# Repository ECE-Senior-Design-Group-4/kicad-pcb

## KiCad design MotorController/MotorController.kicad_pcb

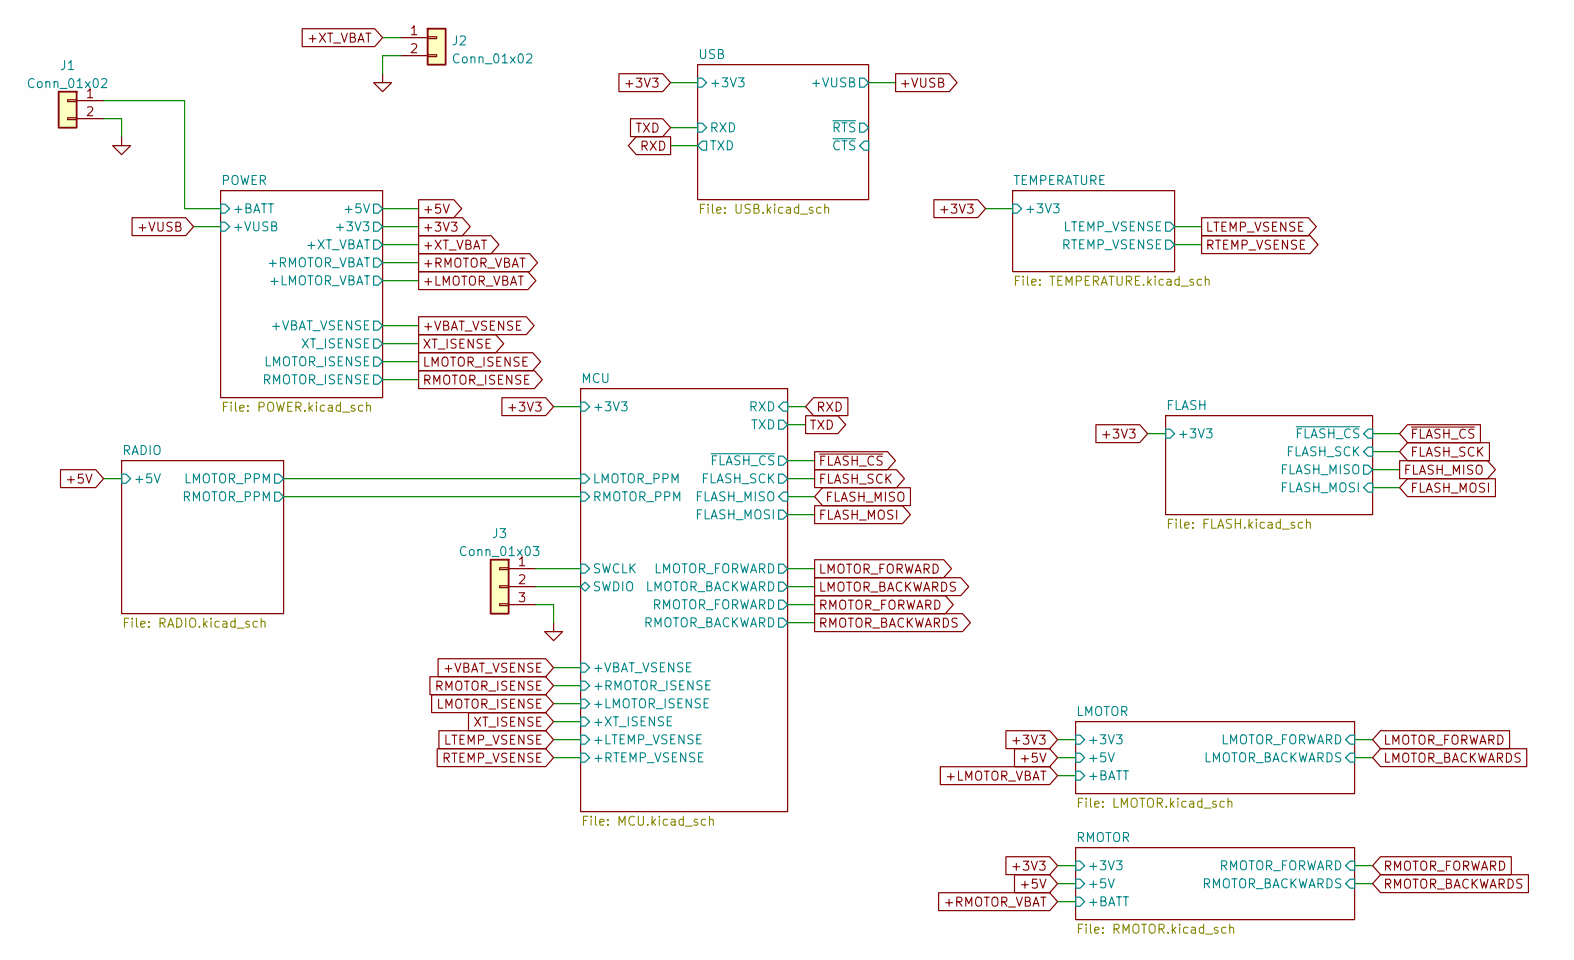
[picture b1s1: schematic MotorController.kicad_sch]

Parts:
J1, J2: Conn_01x02; PinHeader_1x02_P2.54mm_Vertical
J3: Conn_01x03; PinHeader_1x03_P2.54mm_Vertical

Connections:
+XT_VBAT: J2.1; also elsewhere on the board
/MCU/SWCLK: J3.1; also elsewhere on the board
/MCU/SWDIO: J3.2; also elsewhere on the board
GND: J1.2, J2.2, J3.3; also elsewhere on the board

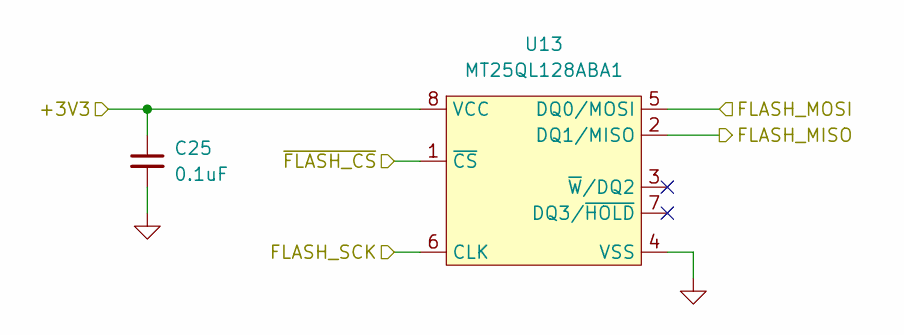
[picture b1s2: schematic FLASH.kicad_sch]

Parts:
C25: 0.1uF; C_0402_1005Metric; MPN CC0402KPX7R8BB104
U13: MT25QL128ABA1; SOIC127P780X200-8N; MPN MT25QL128ABA1

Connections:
+3V3: C25.1, U13.8 (VCC); also elsewhere on the board
FLASH_MISO: U13.2 (DQ1/MISO); also elsewhere on the board
FLASH_MOSI: U13.5 (DQ0/MOSI); also elsewhere on the board
FLASH_SCK: U13.6 (CLK); also elsewhere on the board
GND: C25.2, U13.4 (VSS); also elsewhere on the board
~FLASH_CS: U13.1 (~CS); also elsewhere on the board

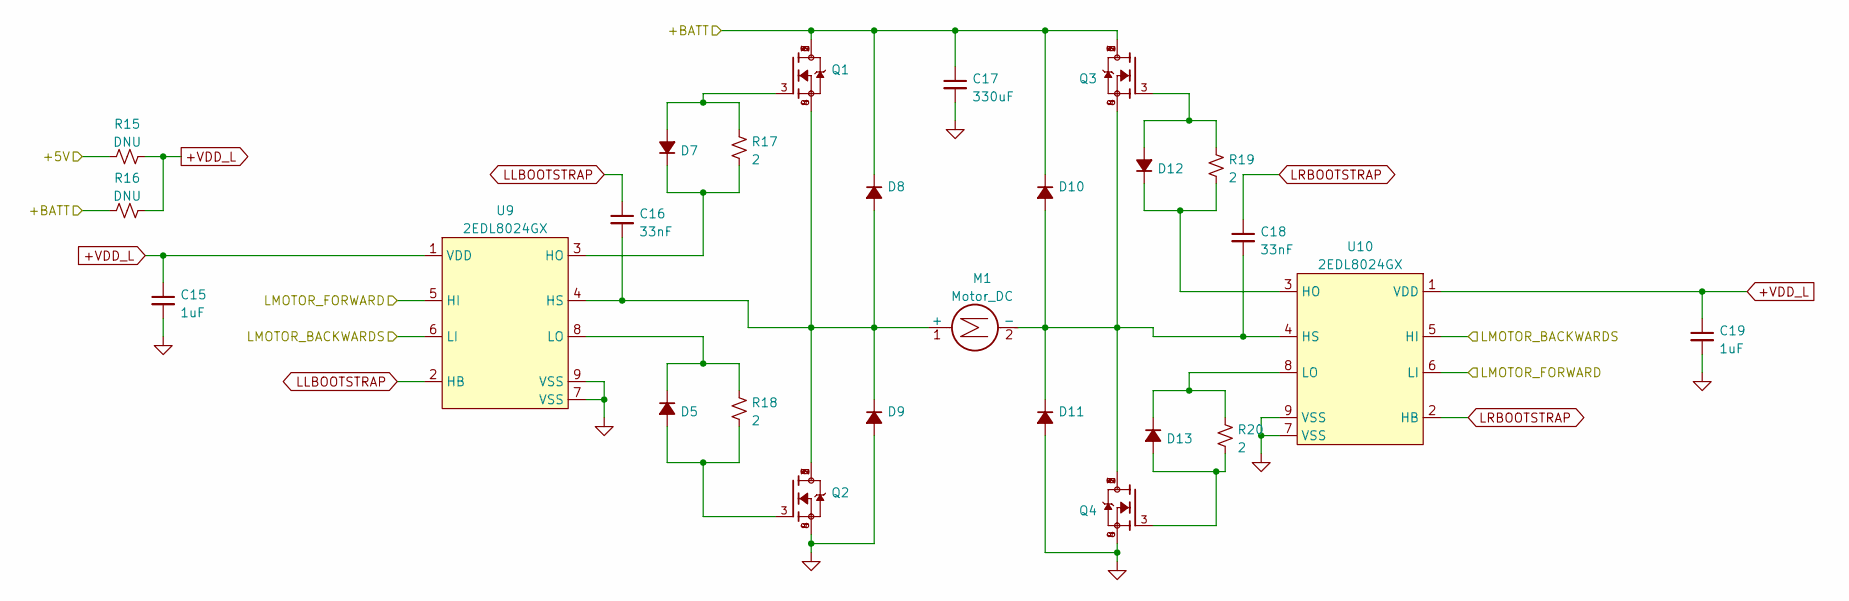
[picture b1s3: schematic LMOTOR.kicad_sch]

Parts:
C15, C19: 1uF; C_0402_1005Metric; MPN CC0402KRX5R8BB105
C16, C18: 33nF; C_0402_1005Metric; MPN CC0402KRX7R9BB333
C17: 330uF; PinHeader_1x02_P2.54mm_Vertical
D5, D7, D12, D13: D_Small_Filled; D_SOD-323; MPN NSR0530HT1G
D8, D9, D10, D11: D_Small_Filled; TO-277B; MPN MBR1560S
M1: Motor_DC; PinHeader_1x02_P2.54mm_Vertical
Q1, Q2, Q3, Q4: SSM6K513NU-LF; TRANS_SSM6K513NU-LF
R15, R16: DNU; R_0402_1005Metric; MPN RC0402JR-0710KL
R17, R18, R19, R20: 2; R_0402_1005Metric; MPN RC0402FR-072RL
U9, U10: 2EDL8024GX; DFN-8-1EP_4x4mm_P0.8mm_EP2.3x3.24mm; MPN 2EDL8024GX

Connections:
+5V: R15.1; also elsewhere on the board
+LMOTOR_VBAT: C17.1, D8.1 (K), D10.1 (K), Q1.1, Q1.2, Q1.5, Q1.6, Q1.7, Q3.1, Q3.2, Q3.5, Q3.6, Q3.7, R16.1; also elsewhere on the board
+VDD_L: C15.1, C19.1, R15.2, R16.2, U9.1 (VDD), U10.1 (VDD)
GND: C15.2, C17.2, C19.2, D9.2 (A), D11.2 (A), Q2.4, Q2.8, Q4.4, Q4.8, U9.7 (VSS), U9.9 (VSS), U10.7 (VSS), U10.9 (VSS); also elsewhere on the board
LLBOOTSTRAP: C16.1, U9.2 (HB)
LMOTOR_BACKWARDS: U9.6 (LI), U10.5 (HI); also elsewhere on the board
LMOTOR_FORWARD: U9.5 (HI), U10.6 (LI); also elsewhere on the board
LRBOOTSTRAP: C18.1, U10.2 (HB)
unnamed: C16.2, D8.2 (A), D9.1 (K), M1.1 (+), Q1.4, Q1.8, Q2.1, Q2.2, Q2.5, Q2.6, Q2.7, U9.4 (HS)
unnamed: C18.2, D10.2 (A), D11.1 (K), M1.2 (-), Q3.4, Q3.8, Q4.1, Q4.2, Q4.5, Q4.6, Q4.7, U10.4 (HS)
unnamed: D5.1 (K), R18.1, U9.8 (LO)
unnamed: D5.2 (A), Q2.3, R18.2
unnamed: D7.1 (K), R17.2, U9.3 (HO)
unnamed: D7.2 (A), Q1.3, R17.1
unnamed: D12.1 (K), R19.2, U10.3 (HO)
unnamed: D12.2 (A), Q3.3, R19.1
unnamed: D13.1 (K), R20.1, U10.8 (LO)
unnamed: D13.2 (A), Q4.3, R20.2

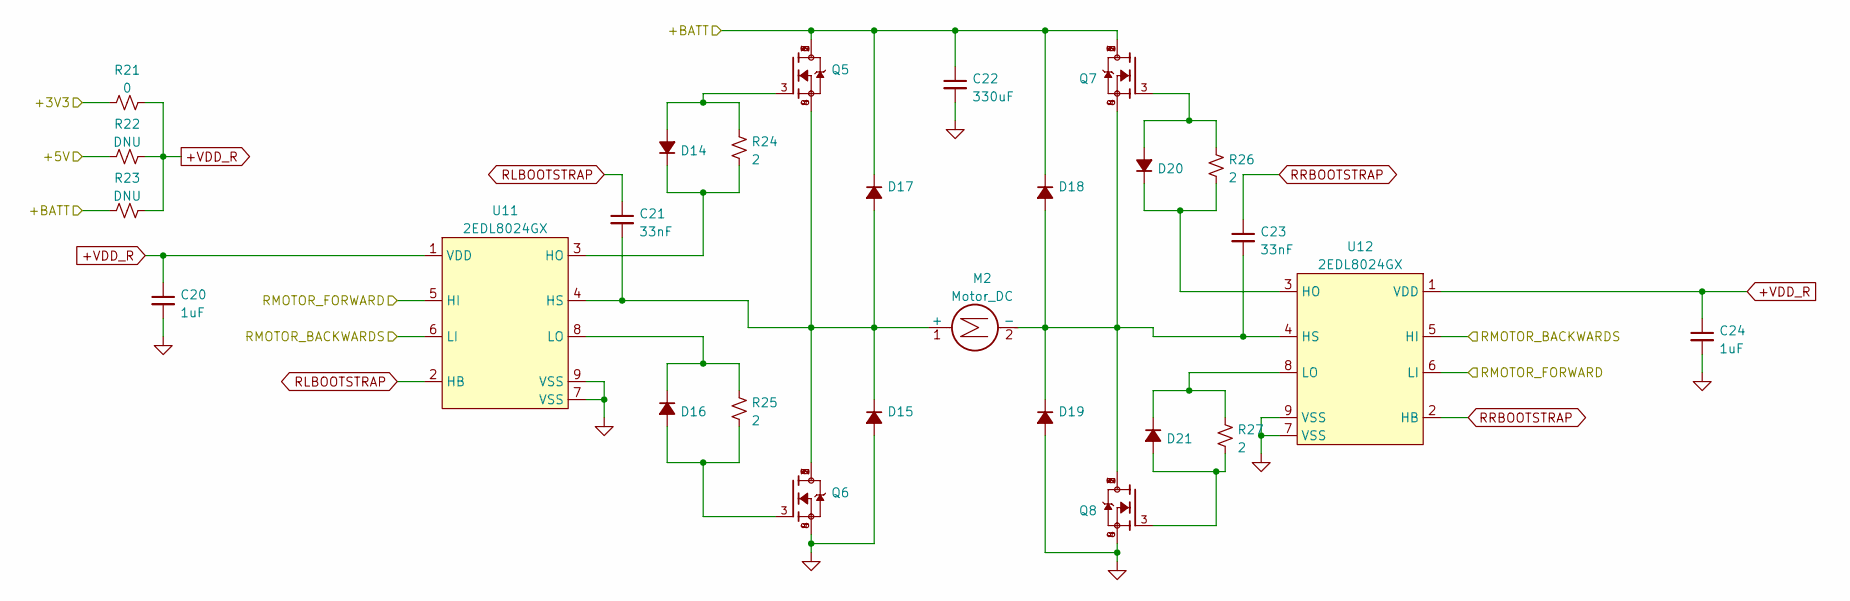
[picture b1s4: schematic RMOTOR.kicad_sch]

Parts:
C20, C24: 1uF; C_0402_1005Metric; MPN CC0402KRX5R8BB105
C21, C23: 33nF; C_0402_1005Metric; MPN CC0402KRX7R9BB333
C22: 330uF; PinHeader_1x02_P2.54mm_Vertical
D14, D16, D20, D21: D_Small_Filled; D_SOD-323; MPN NSR0530HT1G
D15, D17, D18, D19: D_Small_Filled; TO-277B; MPN MBR1560S
M2: Motor_DC; PinHeader_1x02_P2.54mm_Vertical
Q5, Q6, Q7, Q8: SSM6K513NU-LF; TRANS_SSM6K513NU-LF
R21: 0; R_0402_1005Metric; MPN RC0402JR-070RL
R22, R23: DNU; R_0402_1005Metric; MPN RC0402JR-0710KL
R24, R25, R26, R27: 2; R_0402_1005Metric; MPN RC0402FR-072RL
U11, U12: 2EDL8024GX; DFN-8-1EP_4x4mm_P0.8mm_EP2.3x3.24mm; MPN 2EDL8024GX

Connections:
+5V: R22.1; also elsewhere on the board
+VDD_R: C20.1, C24.1, R21.2, R22.2, R23.2, U11.1 (VDD), U12.1 (VDD)
GND: C20.2, C22.2, C24.2, D15.2 (A), D19.2 (A), Q6.4, Q6.8, Q8.4, Q8.8, U11.7 (VSS), U11.9 (VSS), U12.7 (VSS), U12.9 (VSS); also elsewhere on the board
unnamed: C21.2, D15.1 (K), D17.2 (A), M2.1 (+), Q5.4, Q5.8, Q6.1, Q6.2, Q6.5, Q6.6, Q6.7, U11.4 (HS)
unnamed: C23.2, D18.2 (A), D19.1 (K), M2.2 (-), Q7.4, Q7.8, Q8.1, Q8.2, Q8.5, Q8.6, Q8.7, U12.4 (HS)
unnamed: D14.1 (K), R24.2, U11.3 (HO)
unnamed: D14.2 (A), Q5.3, R24.1
unnamed: D16.1 (K), R25.1, U11.8 (LO)
unnamed: D16.2 (A), Q6.3, R25.2
unnamed: D20.1 (K), R26.2, U12.3 (HO)
unnamed: D20.2 (A), Q7.3, R26.1
unnamed: D21.1 (K), R27.1, U12.8 (LO)
unnamed: D21.2 (A), Q8.3, R27.2
RLBOOTSTRAP: C21.1, U11.2 (HB)
RMOTOR_BACKWARDS: U11.6 (LI), U12.5 (HI); also elsewhere on the board
RMOTOR_FORWARD: U11.5 (HI), U12.6 (LI); also elsewhere on the board
RRBOOTSTRAP: C23.1, U12.2 (HB)

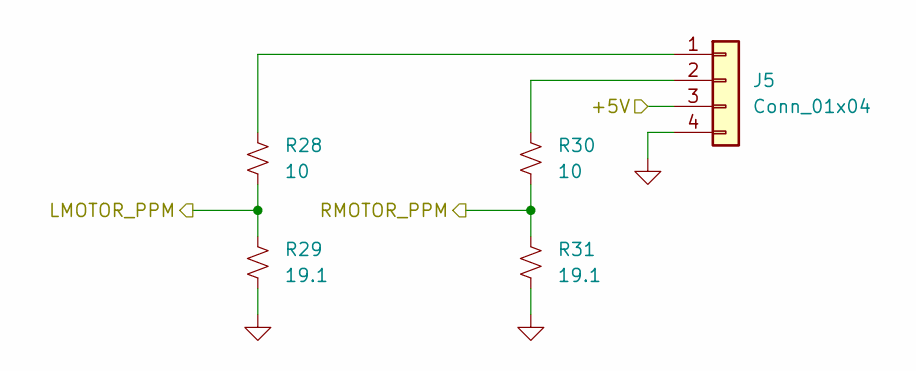
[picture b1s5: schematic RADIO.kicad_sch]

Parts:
J5: Conn_01x04; PinHeader_1x04_P2.54mm_Vertical
R28, R30: 10; R_0402_1005Metric; MPN RC0402JR-0710RL
R29, R31: 19.1; R_0402_1005Metric; MPN RC0402FR-0719R1L

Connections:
+5V: J5.3; also elsewhere on the board
/MCU/LMOTOR_PPM: R28.2, R29.1; also elsewhere on the board
/MCU/RMOTOR_PPM: R30.2, R31.1; also elsewhere on the board
GND: J5.4, R29.2, R31.2; also elsewhere on the board
unnamed: J5.1, R28.1
unnamed: J5.2, R30.1

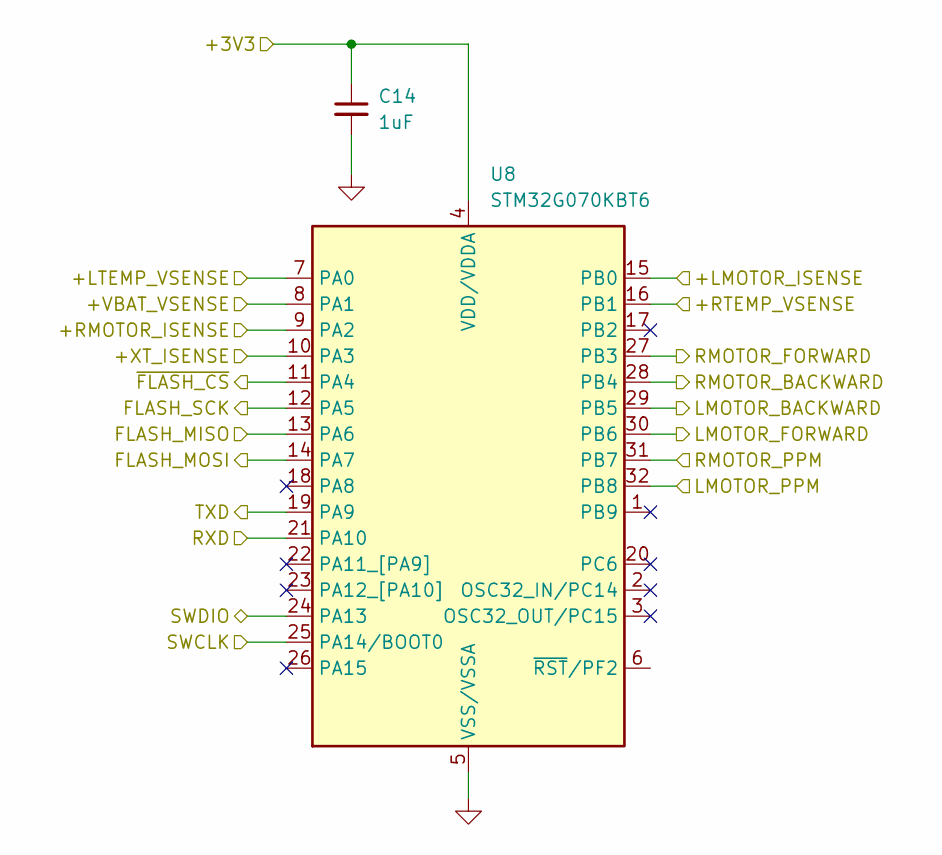
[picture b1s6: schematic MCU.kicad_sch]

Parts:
C14: 1uF; C_0402_1005Metric; MPN CC0402KRX5R8BB105
U8: STM32G070KBT6; LQFP-32_7x7mm_P0.8mm; MPN STM32G070KBT6

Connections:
+3V3: C14.1, U8.4 (VDD/VDDA); also elsewhere on the board
+VBAT_VSENSE: U8.8 (PA1); also elsewhere on the board
/MCU/LMOTOR_PPM: U8.32 (PB8); also elsewhere on the board
/MCU/RMOTOR_PPM: U8.31 (PB7); also elsewhere on the board
/MCU/SWCLK: U8.25 (PA14/BOOT0); also elsewhere on the board
/MCU/SWDIO: U8.24 (PA13); also elsewhere on the board
FLASH_MISO: U8.13 (PA6); also elsewhere on the board
FLASH_MOSI: U8.14 (PA7); also elsewhere on the board
FLASH_SCK: U8.12 (PA5); also elsewhere on the board
GND: C14.2, U8.5 (VSS/VSSA); also elsewhere on the board
LMOTOR_BACKWARDS: U8.30 (PB6); also elsewhere on the board
LMOTOR_FORWARD: U8.29 (PB5); also elsewhere on the board
LMOTOR_ISENSE: U8.9 (PA2); also elsewhere on the board
LTEMP_VSENSE: U8.7 (PA0); also elsewhere on the board
RMOTOR_BACKWARDS: U8.27 (PB3); also elsewhere on the board
RMOTOR_FORWARD: U8.28 (PB4); also elsewhere on the board
RMOTOR_ISENSE: U8.15 (PB0); also elsewhere on the board
RTEMP_VSENSE: U8.16 (PB1); also elsewhere on the board
RXD: U8.21 (PA10); also elsewhere on the board
TXD: U8.19 (PA9); also elsewhere on the board
XT_ISENSE: U8.10 (PA3); also elsewhere on the board
~FLASH_CS: U8.11 (PA4); also elsewhere on the board

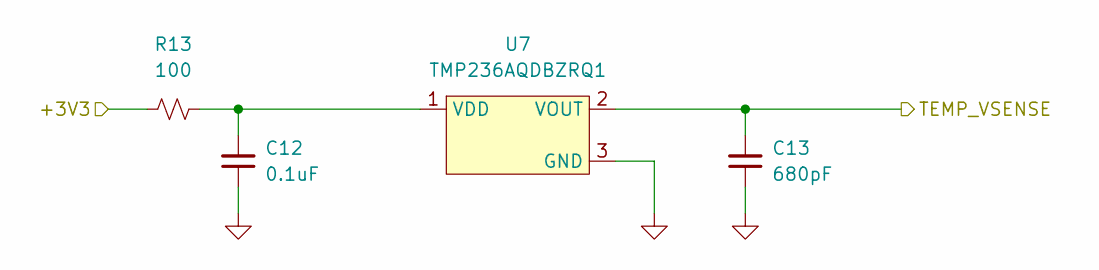
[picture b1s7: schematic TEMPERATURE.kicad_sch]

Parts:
C12: 0.1uF; C_0603_1608Metric; MPN CC0603JRX7R8BB104
C13: 680pF; C_0603_1608Metric; MPN CC0603JRNPO8BN681
R13: 100; R_0603_1608Metric; MPN RC0603FR-07100RL
U7: TMP236AQDBZRQ1; SC-59; MPN TMP236AQDBZRQ1

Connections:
+3V3: R13.1; also elsewhere on the board
GND: C12.1, C13.1, U7.3 (GND); also elsewhere on the board
LTEMP_VSENSE: C13.2, U7.2 (VOUT); also elsewhere on the board
unnamed: C12.2, R13.2, U7.1 (VDD)

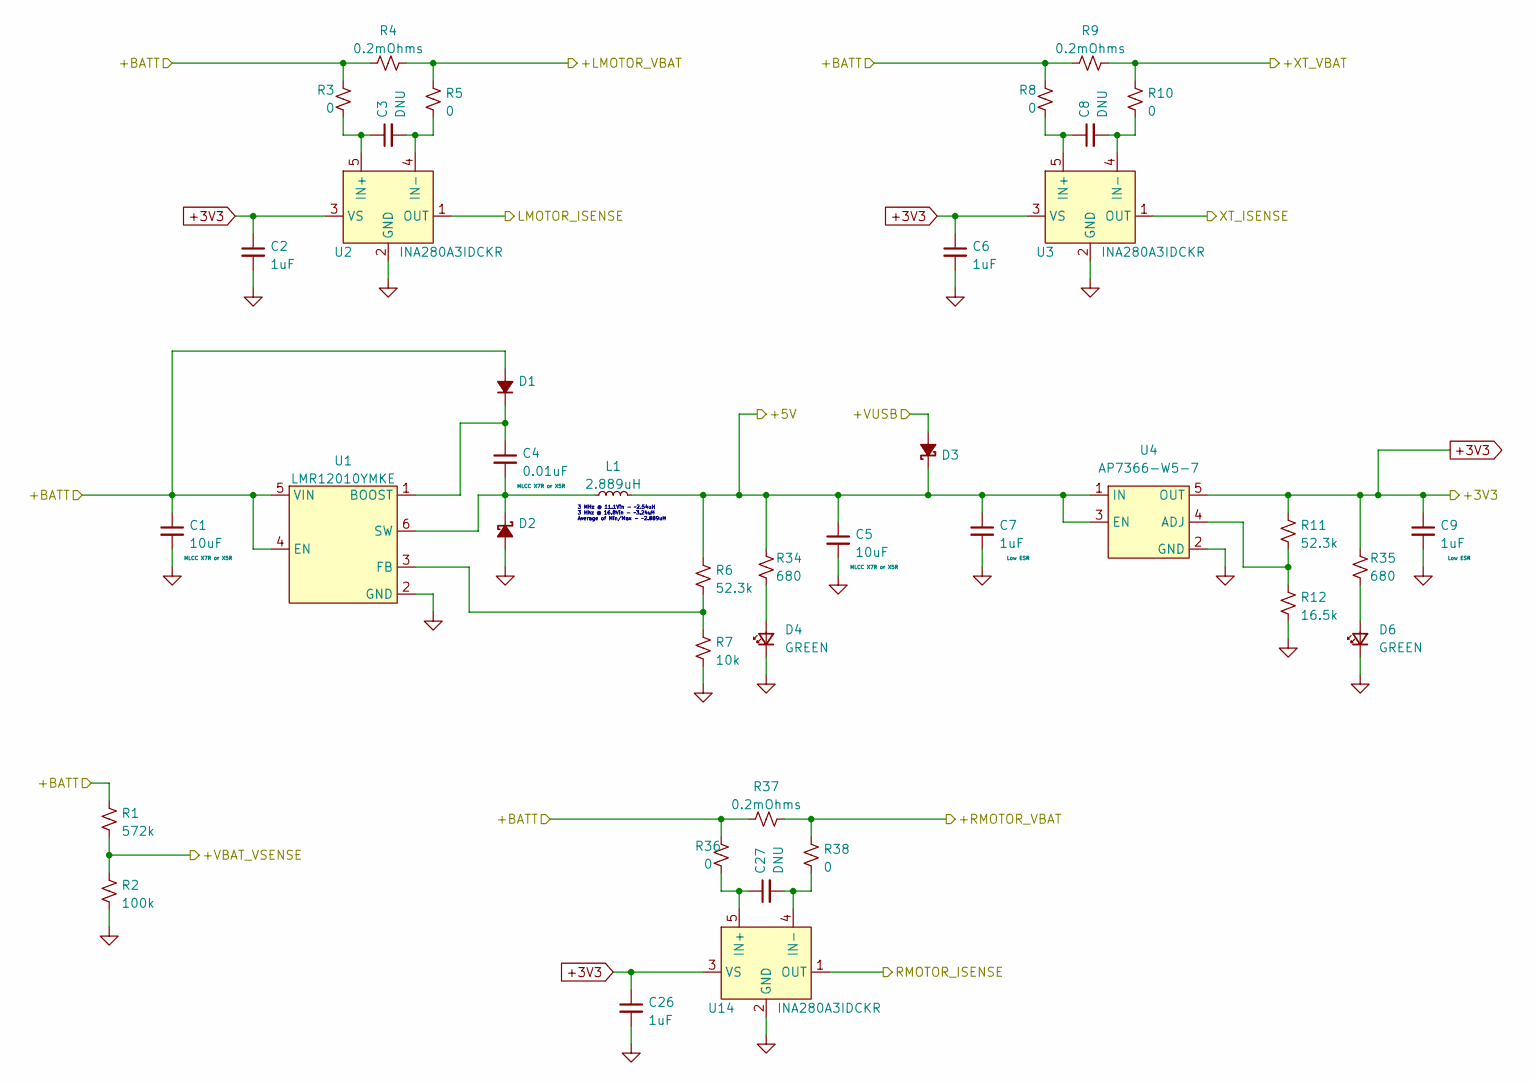
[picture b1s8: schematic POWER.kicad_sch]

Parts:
C1, C5: 10uF; C_0603_1608Metric; MPN CC0603MRX5R8BB106
C2, C6, C7, C9, C26: 1uF; C_0402_1005Metric; MPN CC0402KRX5R8BB105
C3, C8, C27: DNU; C_0402_1005Metric
C4: 0.01uF; C_0402_1005Metric; MPN CC0402KRX7R8BB103
D1: D_Small_Filled; D_SMA; MPN S1A-13-F
D2, D3: D_Schottky_Small_Filled; D_SOD-123F; MPN CRS06(TE85L,Q,M)
D4, D6: GREEN; LED_0603_1608Metric; MPN 150060VS75000
L1: 2.889uH; XGL5050-282MEC; MPN XGL5050-282MEC
R1: 572k; R_0402_1005Metric; MPN RC0402FR-07576KL
R2: 100k; R_0402_1005Metric; MPN RC0402JR-07100KL
R3, R5, R8, R10, R36, R38: 0; R_0402_1005Metric; MPN RC0402JR-070RL
R4, R9, R37: 0.2mOhms; RES_WSK12161L000FEA; MPN WSK1216L2000FEA
R6, R11: 52.3k; R_0402_1005Metric; MPN RC0402FR-0752K3L
R7: 10k; R_0402_1005Metric; MPN RC0402JR-0710KL
R12: 16.5k; R_0402_1005Metric; MPN RC0402FR-0716K5L
R34, R35: 680; R_0402_1005Metric; MPN RC0402FR-07680RL
U1: LMR12010YMKE; TSOT-23-6; MPN LMR12010YMKE
U2, U3, U14: INA280A3IDCKR; SOT-353_SC-70-5; MPN INA280A3IDCKR
U4: AP7366-W5-7; MPN AP7366-W5-7

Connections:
+3V3: C2.1, C6.1, C9.1, C26.1, R11.1, R35.2, U2.3 (VS), U3.3 (VS), U4.5 (OUT), U14.3 (VS); also elsewhere on the board
+5V: C5.1, C7.1, D3.1 (K), L1.2, R6.1, R34.2, U4.1 (IN), U4.3 (EN); also elsewhere on the board
+LMOTOR_VBAT: R4.2, R5.2; also elsewhere on the board
+VBAT_VSENSE: R1.2, R2.1; also elsewhere on the board
+VUSB: D3.2 (A); also elsewhere on the board
+XT_VBAT: R9.2, R10.2; also elsewhere on the board
GND: C1.2, C2.2, C5.2, C6.2, C7.2, C9.2, C26.2, D2.2 (A), D4.1 (K), D6.1 (K), R2.2, R7.2, R12.2, U1.2 (GND), U2.2 (GND), U3.2 (GND), U4.2 (GND), U14.2 (GND); also elsewhere on the board
LMOTOR_ISENSE: U2.1 (OUT); also elsewhere on the board
unnamed: C3.1, R3.2, U2.5 (IN+)
unnamed: C3.2, R5.1, U2.4 (IN-)
unnamed: C4.1, D1.1 (K), U1.1 (BOOST)
unnamed: C4.2, D2.1 (K), L1.1, U1.6 (SW)
unnamed: C8.1, R8.2, U3.5 (IN+)
unnamed: C8.2, R10.1, U3.4 (IN-)
unnamed: C27.1, R36.2, U14.5 (IN+)
unnamed: C27.2, R38.1, U14.4 (IN-)
unnamed: D4.2 (A), R34.1
unnamed: D6.2 (A), R35.1
unnamed: R6.2, R7.1, U1.3 (FB)
unnamed: R11.2, R12.1, U4.4 (ADJ)
RMOTOR_ISENSE: U14.1 (OUT); also elsewhere on the board
XT_ISENSE: U3.1 (OUT); also elsewhere on the board

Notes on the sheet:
3 MHz @ 11.1Vin - ~2.54uH 3 Mhz @ 16.8Vin - ~3.24uH Average of Min/Max - ~2.889uH

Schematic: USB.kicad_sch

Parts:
C10: 1uF; C_0402_1005Metric; MPN CC0402KRX5R8BB105
C11: 0.1uF; C_0402_1005Metric; MPN CC0402KPX7R8BB104
J4: USB_B_Micro; CUI_UJ2-MIBH-G-SMT-TR; MPN UJ2-MIBH-G-SMT-TR
U5: TPD2E2U06DCKR; SOT-323_SC-70; MPN TPD2E2U06DCKR
U6: FT234XD-R; DFN-12-1EP_3x3mm_P0.5mm_EP1.6x2.5mm; MPN FT234XD-R

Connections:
+3V3: C10.1, C11.1, U6.2 (~RESET), U6.3 (3V3OUT), U6.4 (VCC), U6.9 (VCCIO); also elsewhere on the board
+VUSB: J4.1 (VBUS); also elsewhere on the board
GND: C10.2, C11.2, J4.5 (GND), J4.6 (Shield), U5.3 (GND), U6.5 (GND), U6.13 (GND); also elsewhere on the board
RXD: U6.7 (TXD); also elsewhere on the board
TXD: U6.10 (RXD); also elsewhere on the board

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
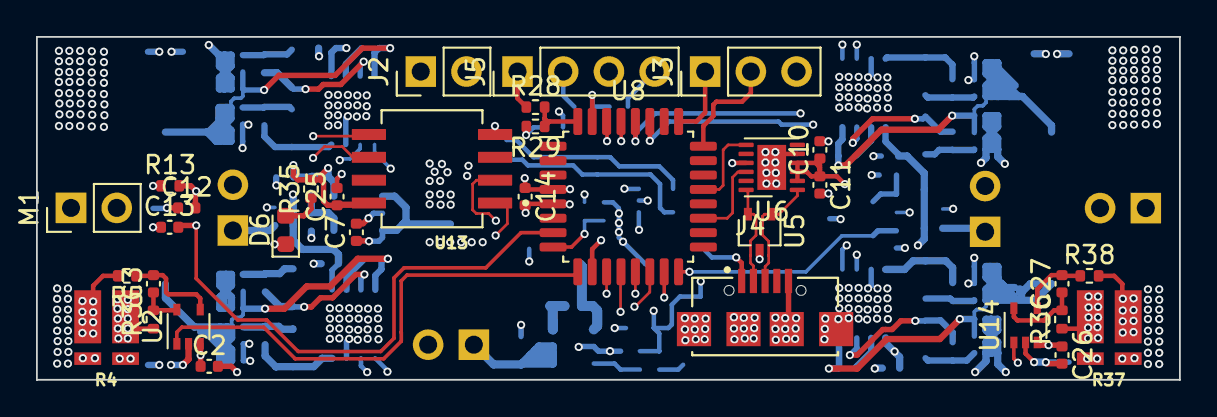
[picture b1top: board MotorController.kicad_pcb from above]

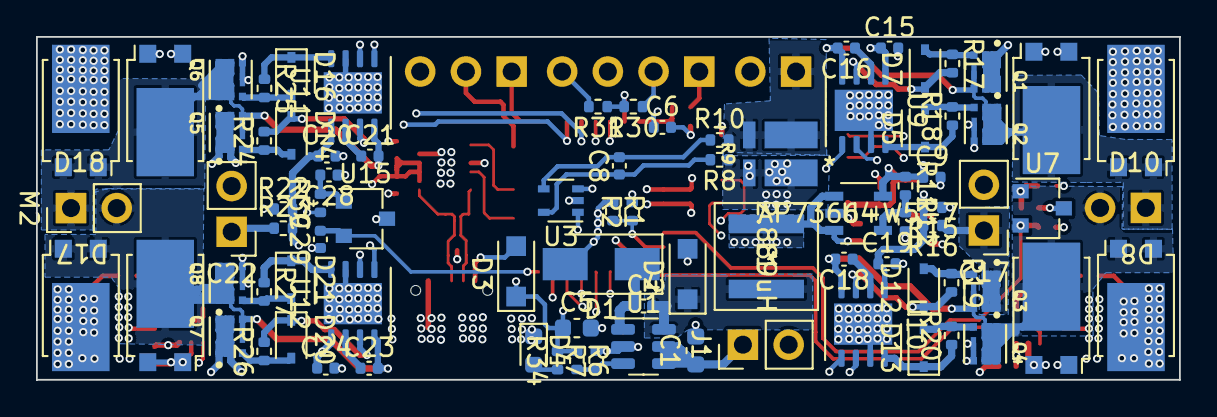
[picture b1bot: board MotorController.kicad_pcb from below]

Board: 6 copper layers, 63.5 x 19.0 mm, 116 parts (83 on the bottom side), 72 nets.

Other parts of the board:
C28: 0.1uF; C_0402_1005Metric
C29: 680pF; C_0402_1005Metric
R39: 100; R_0402_1005Metric
U15: TMP236AQDBZRQ1; SC-59

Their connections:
+3V3: R39.1; also elsewhere on the board
GND: C28.1, C29.1, U15.3 (GND); also elsewhere on the board
unnamed: C28.2, R39.2, U15.1 (VDD)
RTEMP_VSENSE: C29.2, U15.2 (VOUT); also elsewhere on the board

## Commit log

2023-01-19 Added Hierarchal Sheets
    Added Hierarchal Sheets for each component block (based on the "UpdatedBlockDiagram.png"
2023-02-02 Lots of Updates
2023-02-02 Schematic Updates
2023-02-02 Updates
    Updates
2023-02-07 More updates
2023-02-14 Changes
    Changes
2023-02-16 So many updates
2023-02-18 my god
    my god
2023-02-18 The monstrosity is almost done
    The monstrosity is almost done
2023-02-20 ahhhhh
2023-03-02 FIn
    Fin

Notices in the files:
parts and their libraries:
Copyright 2021 Accelerated Designs. All rights reserved.
